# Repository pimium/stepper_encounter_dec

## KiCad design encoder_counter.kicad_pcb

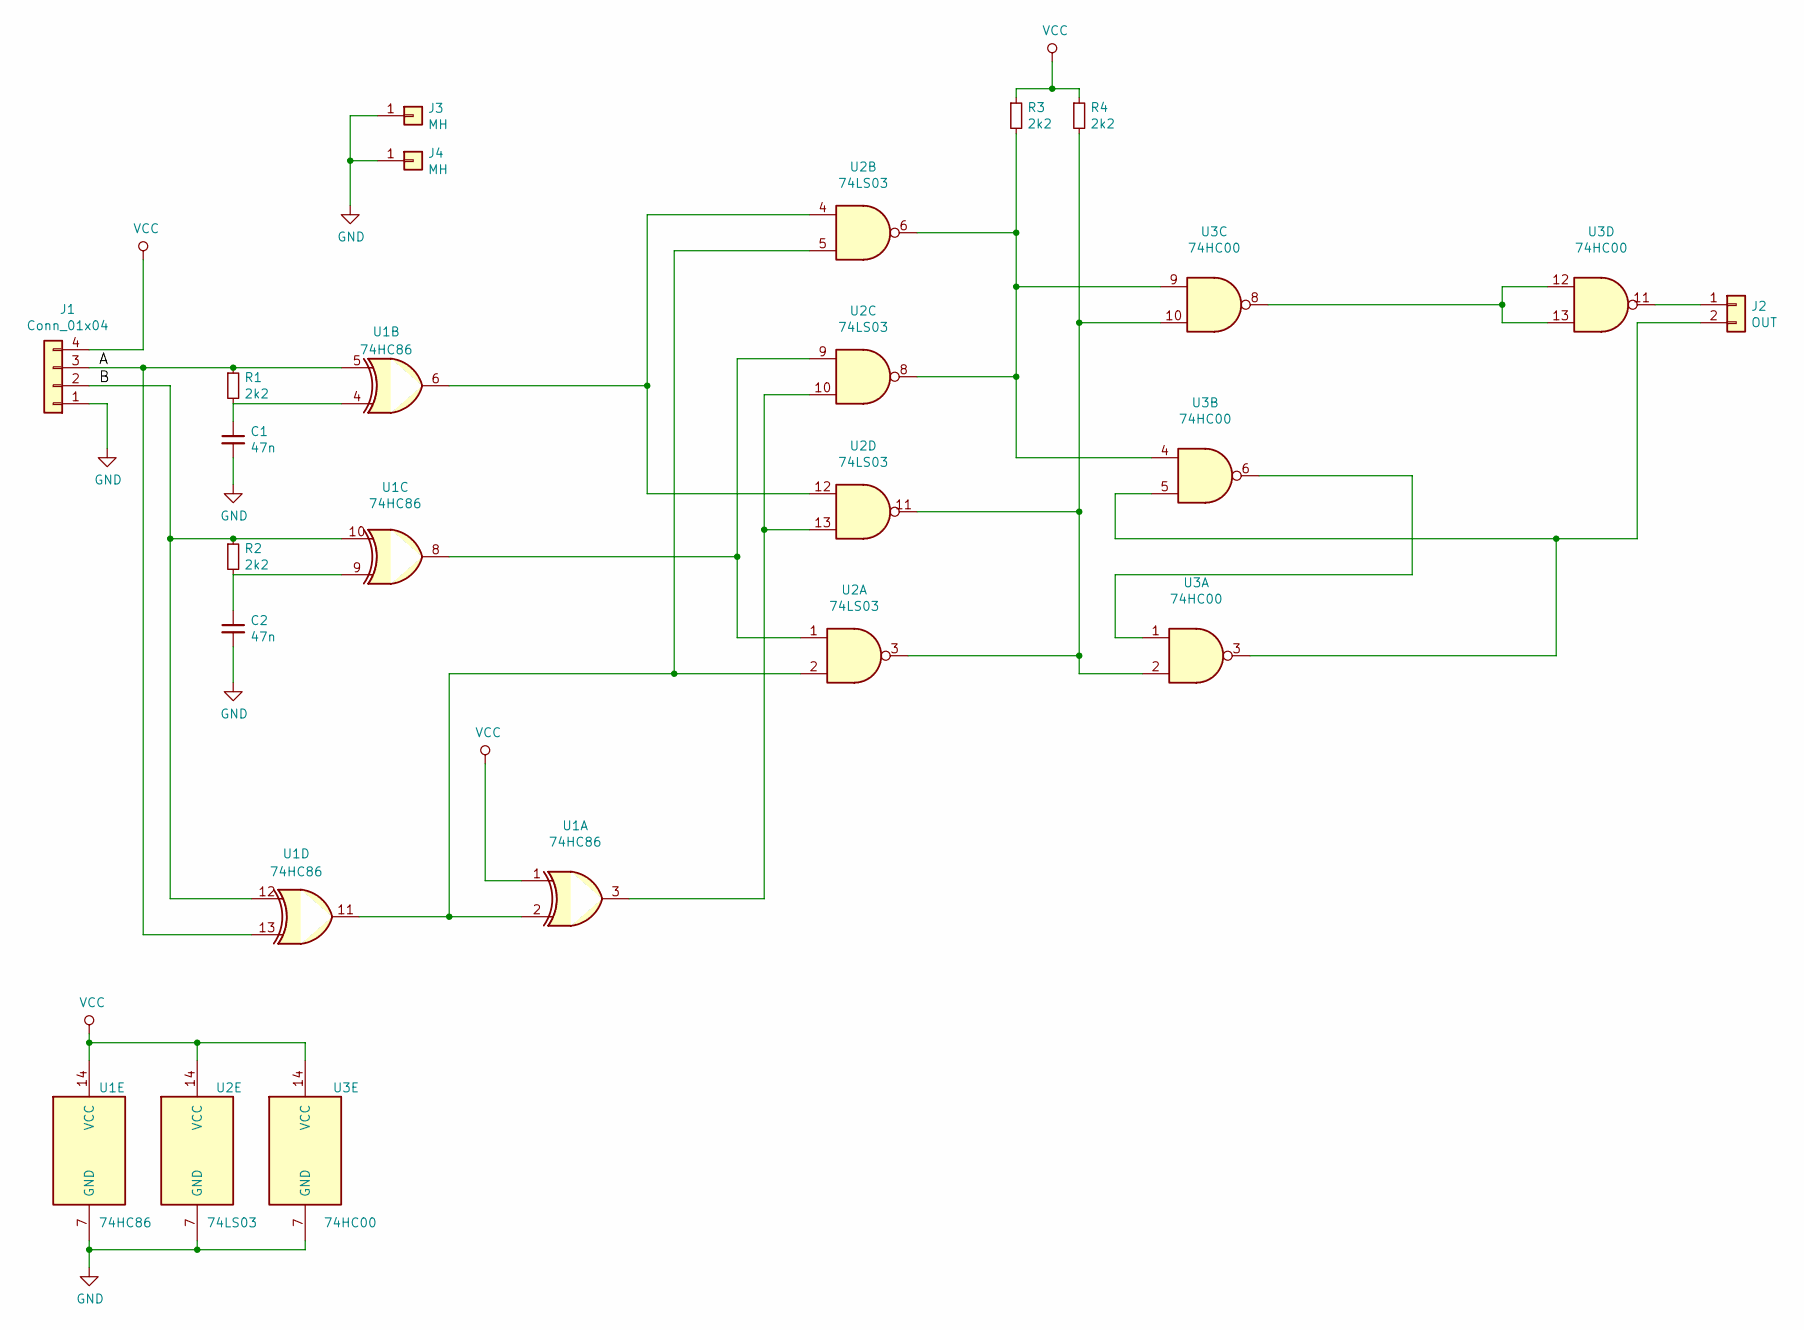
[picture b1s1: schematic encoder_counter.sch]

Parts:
C1, C2: 47n; C_0805_HandSoldering
J1: Conn_01x04; Pin_Header_Straight_1x04_Pitch2.54mm
J2: OUT; Pin_Header_Straight_1x02_Pitch2.54mm
J3, J4: MH; MountingHole_3.2mm_M3_ISO14580_Pad
R1, R2, R3, R4: 2k2; R_0805_HandSoldering
U1: 74HC86; DIP-14_W7.62mm
U2: 74LS03; DIP-14_W7.62mm
U3: 74HC00; DIP-14_W7.62mm

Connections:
/A: J1.3, R1.1, U1.5, U1.13
/B: J1.2, R2.1, U1.10, U1.12
GND: C1.2, C2.2, J1.1, J3.1, J4.1, U1.7 (GND), U2.7 (GND), U3.7 (GND)
unnamed: C1.1, R1.2, U1.4
unnamed: C2.1, R2.2, U1.9
unnamed: J2.1, U3.11
unnamed: J2.2, U3.3, U3.5
unnamed: R3.2, U2.6, U2.8, U3.4, U3.9
unnamed: R4.2, U2.3, U2.11, U3.2, U3.10
unnamed: U1.3, U2.10, U2.13
unnamed: U1.6, U2.4, U2.12
unnamed: U1.8, U2.1, U2.9
unnamed: U1.2, U1.11, U2.2, U2.5
unnamed: U3.1, U3.6
unnamed: U3.8, U3.12, U3.13
VCC: J1.4, R3.1, R4.1, U1.1, U1.14 (VCC), U2.14 (VCC), U3.14 (VCC)

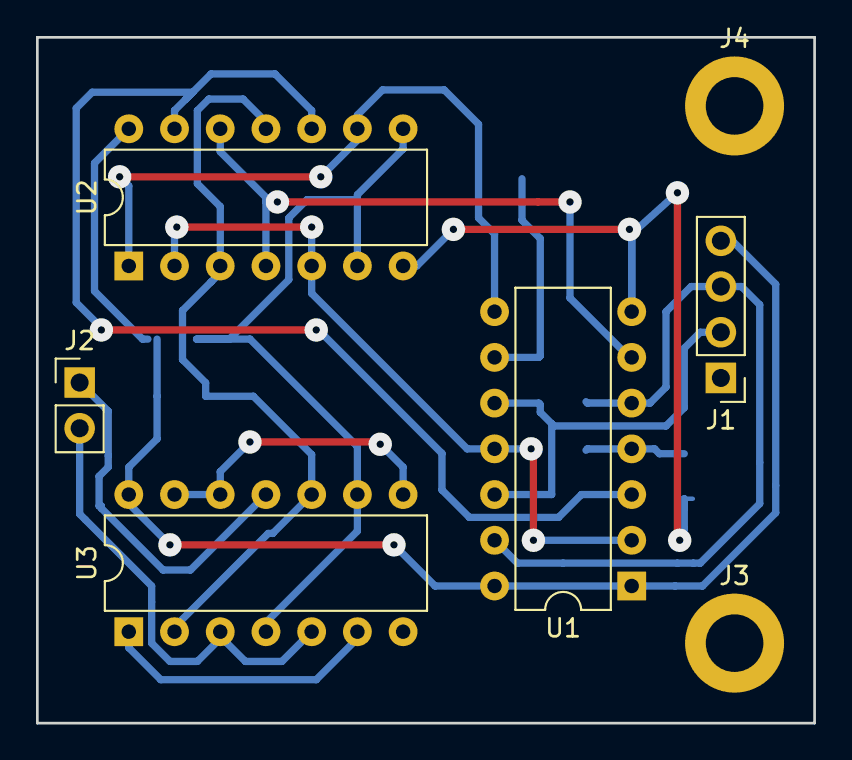
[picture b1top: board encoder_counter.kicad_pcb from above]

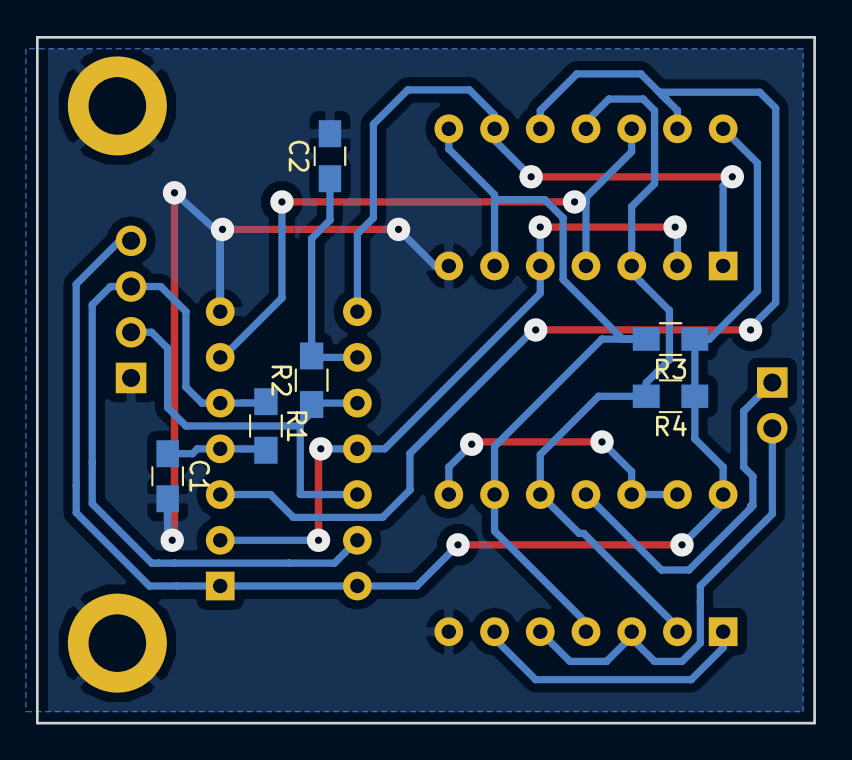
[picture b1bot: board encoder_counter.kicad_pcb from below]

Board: 2 copper layers, 43.2 x 38.1 mm, 13 parts (6 on the bottom side), 16 nets.
